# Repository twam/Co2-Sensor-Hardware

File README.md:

Co2-Sensor-Hardware
===

This repository is the hoftware part of the software project https://github.com/twam/Co2-Sensor-Software.

### Images

### JLCPCB

PCBs can be ordered almost fully-assembled from [JLCPCB](https://jlcpcb.com/DDE). Required files are
[Co2-Sensor_bom_jlc.csv](Gerber/Co2-Sensor_bom_jlc.csv), [Co2-Sensor_cpl_jlc.csv](Gerber/Co2-Sensor_cpl_jlc.csv) and
[Co2-Sensor.zip](Co2-Sensor.zip). Components missing are
* Co2 Sensor (J2)
* USB connector (J5) – can be also populated in the mean time, but is not included in production files, yet.

## License

[![CC BY-SA 4.0][cc-by-sa-shield]][cc-by-sa]

This work is licensed under a [Creative Commons Attribution-NonCommercial-ShareAlike 4.0 International License][cc-by-sa].

[![CC BY-SA 4.0][cc-by-sa-image]][cc-by-sa]

[cc-by-sa]: http://creativecommons.org/licenses/by-nc-sa/4.0/
[cc-by-sa-image]: https://licensebuttons.net/l/by-nc-sa/4.0/88x31.png
[cc-by-sa-shield]: https://img.shields.io/badge/License-CC%20BY--NC--SA%204.0-lightgrey.svg

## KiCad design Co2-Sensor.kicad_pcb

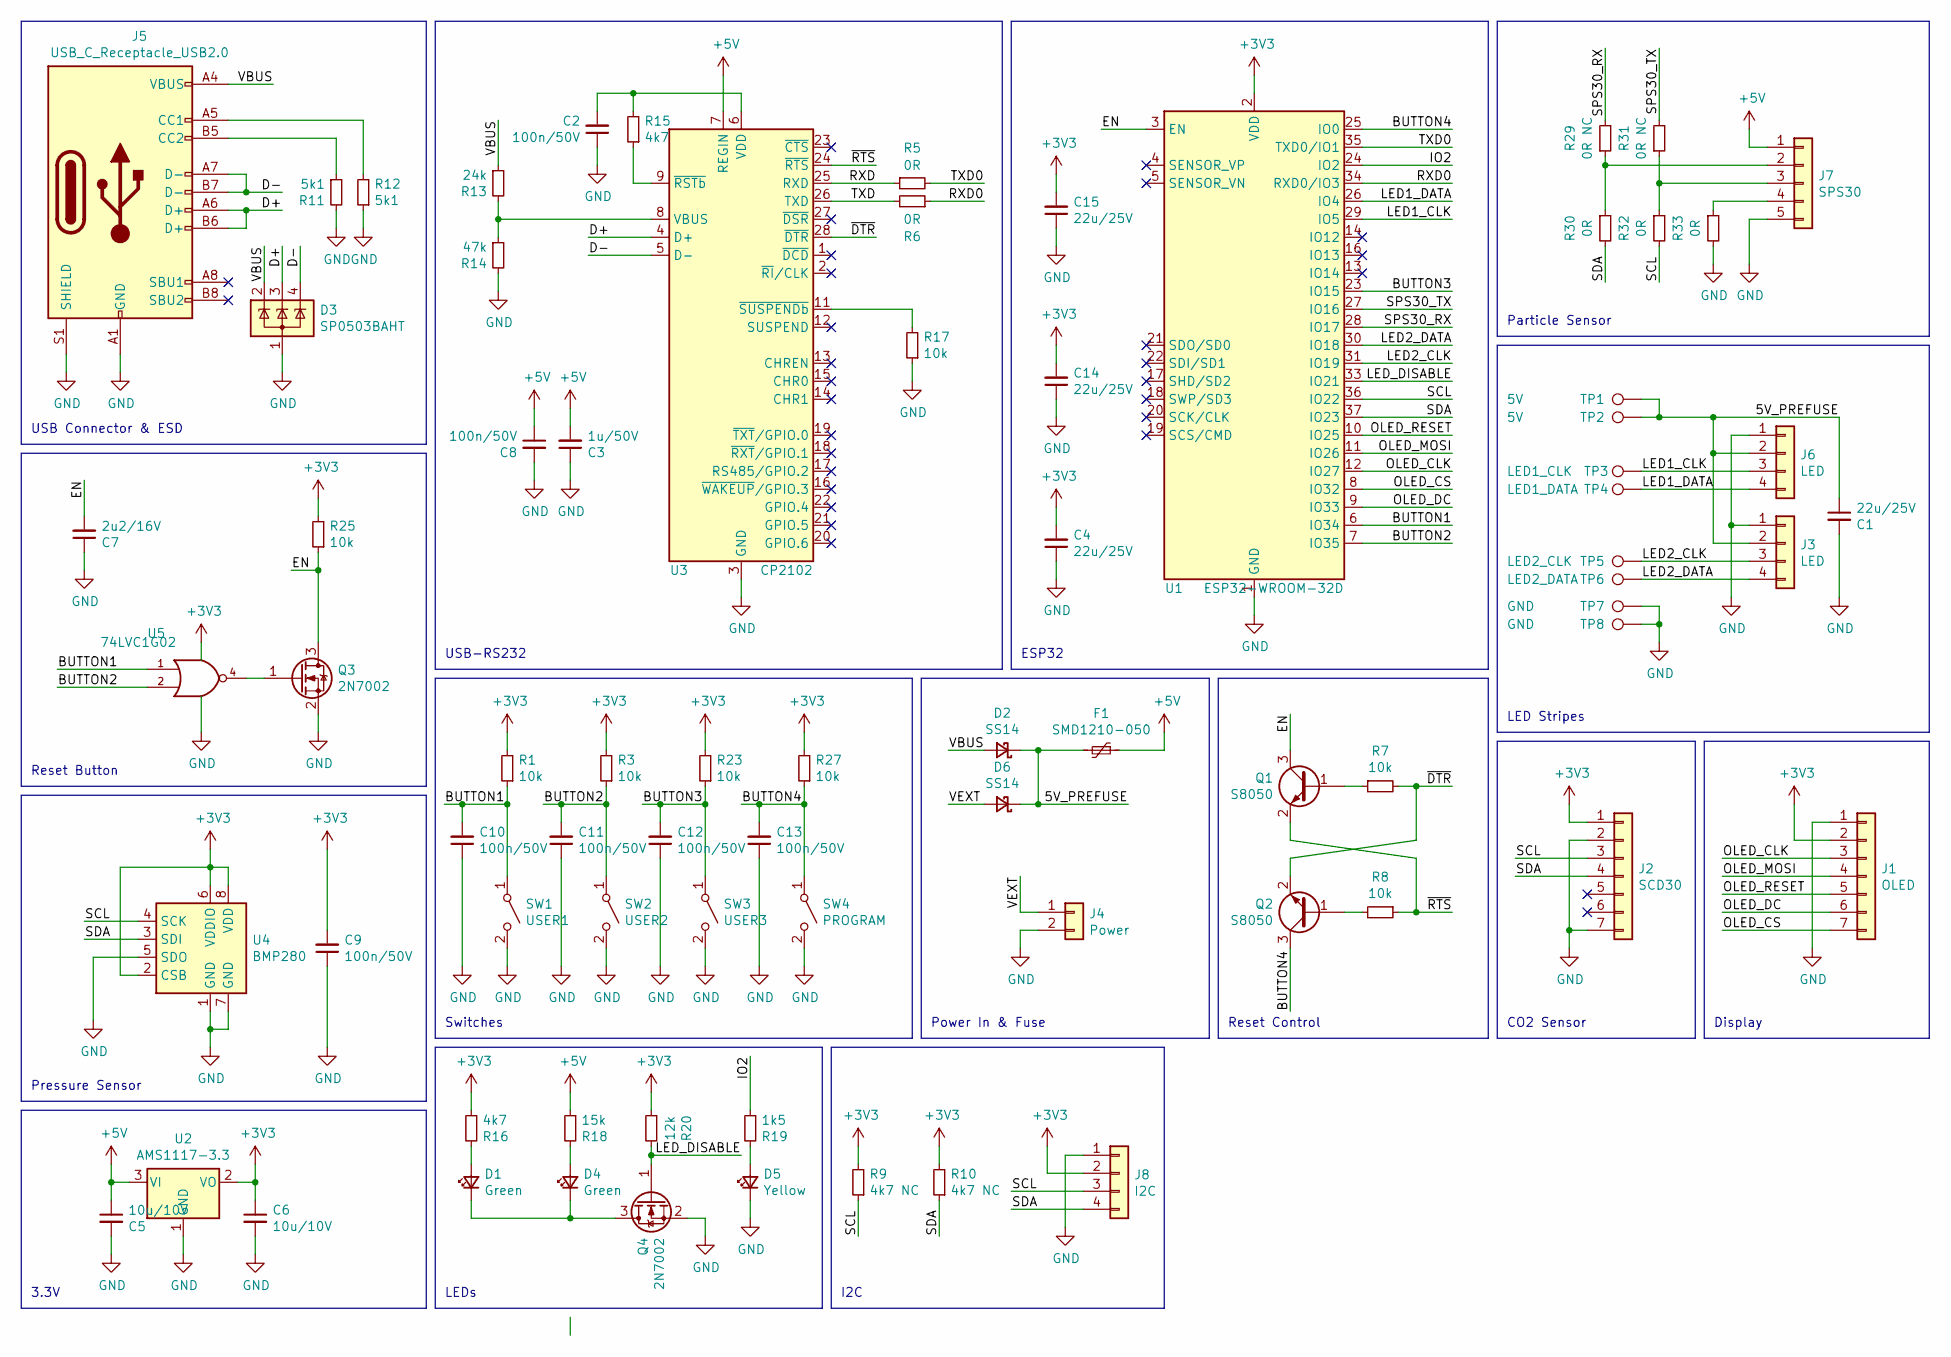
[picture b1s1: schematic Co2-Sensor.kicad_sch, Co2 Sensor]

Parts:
C1, C4, C14, C15: 22u/25V; C_0805_2012Metric; LCSC C45783
C2, C8, C9, C10, C11, C12, C13: 100n/50V; C_0603_1608Metric; LCSC C14663
C3: 1u/50V; C_0603_1608Metric; LCSC C15849
C5, C6: 10u/10V; C_0603_1608Metric; LCSC C19702
C7: 2u2/16V; C_0603_1608Metric; LCSC C23630
D1, D4: Green; LED_0603_1608Metric; LCSC C72043
D2, D6: SS14; D_SMA; LCSC C2480
D3: SP0503BAHT; SOT-143; LCSC C7074
D5: Yellow; LED_0603_1608Metric; LCSC C72038
F1: SMD1210-050; Fuse_1210_3225Metric; LCSC C70094
J1: OLED; TZT_154
J2: SCD30; Sensiron_SCD30
J3, J6: LED; PinHeader_1x04_P2.54mm_Horizontal
J4: Power; PinHeader_1x02_P2.54mm_Horizontal
J5: USB_C_Receptacle_USB2.0; USB_C_Receptacle_XKB_U262-16XN-4BVC11
J7: SPS30; PinHeader_1x05_P2.54mm_Horizontal
J8: I2C; PinHeader_1x04_P2.54mm_Horizontal
Q1, Q2: S8050; SOT-23; LCSC C2146
Q3, Q4: 2N7002; SOT-23; LCSC C8545
R1, R3, R7, R8, R17, R23, R25, R27: 10k; R_0603_1608Metric; LCSC C25804
R5, R6, R30, R32, R33: 0R; R_0603_1608Metric; LCSC C21189
R9, R10: 4k7 NC; R_0603_1608Metric
R11, R12: 5k1; R_0603_1608Metric; LCSC C23186
R13: 24k; R_0603_1608Metric; LCSC C23352
R14: 47k; R_0603_1608Metric; LCSC C25819
R15, R16: 4k7; R_0603_1608Metric; LCSC C23162
R18: 15k; R_0603_1608Metric; LCSC C22809
R19: 1k5; R_0603_1608Metric; LCSC C22843
R20: 12k; R_0603_1608Metric; LCSC C22790
R29, R31: 0R NC; R_0603_1608Metric
SW1: USER1; SW_SPST_XKB_TS-1187A-X-X-X; LCSC C318886
SW2: USER2; SW_SPST_XKB_TS-1187A-X-X-X; LCSC C318886
SW3: USER3; SW_SPST_XKB_TS-1187A-X-X-X; LCSC C318886
SW4: PROGRAM; SW_SPST_XKB_TS-1187A-X-X-X; LCSC C318886
TP1, TP2: 5V; TestPoint_Pad_2.5x2.5mm
TP3: LED1_CLK; TestPoint_Pad_2.5x2.5mm
TP4: LED1_DATA; TestPoint_Pad_2.5x2.5mm
TP5: LED2_CLK; TestPoint_Pad_2.5x2.5mm
TP6: LED2_DATA; TestPoint_Pad_2.5x2.5mm
TP7, TP8: GND; TestPoint_Pad_2.5x2.5mm
U1: ESP32-WROOM-32D; ESP32-WROOM-32
U2: AMS1117-3.3; SOT-223-3_TabPin2; LCSC C6186
U3: CP2102; QFN-28-1EP_5x5mm_P0.5mm_EP3.35x3.35mm; LCSC C6568
U4: BMP280; Bosch_LGA-8_2x2.5mm_P0.65mm_ClockwisePinNumbering; LCSC C83291
U5: 74LVC1G02; SOT-23-5; LCSC C16360

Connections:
+3V3: C4.2, C6.1, C9.2, C14.2, C15.2, J1.2, J2.1, J8.2, R1.2, R3.2, R9.2, R10.2, R16.1, R20.1, R23.2, R25.2, R27.2, U1.2 (VDD), U2.2 (VO), U4.2 (CSB), U4.6 (VDDIO), U4.8 (VDD), U5.5 (VCC)
+5V: C3.2, C5.1, C8.1, F1.1, J7.1, R18.1, U2.3 (VI), U3.7 (REGIN)
/5V_PREFUSE: C1.1, D2.1 (K), D6.1 (K), F1.2, J3.2, J6.2, TP1.1, TP2.1
/BUTTON1: C10.2, R1.1, SW1.1 (A), U1.6 (IO34), U5.1
/BUTTON2: C11.2, R3.1, SW2.1 (A), U1.7 (IO35), U5.2
/BUTTON3: C12.2, R23.1, SW3.1 (A), U1.23 (IO15)
/BUTTON4: C13.2, Q2.3 (C), R27.1, SW4.1 (A), U1.25 (IO0)
/D+: D3.3 (K), J5.A6 (D+), J5.B6 (D+), U3.4 (D+)
/D-: D3.4 (K), J5.A7 (D-), J5.B7 (D-), U3.5 (D-)
/EN: C7.2, Q1.3 (C), Q3.3 (D), R25.1, U1.3 (EN)
/IO2: R19.1, U1.24 (IO2)
/LED1_CLK: J6.3, TP3.1, U1.29 (IO5)
/LED1_DATA: J6.4, TP4.1, U1.26 (IO4)
/LED2_CLK: J3.3, TP5.1, U1.31 (IO19)
/LED2_DATA: J3.4, TP6.1, U1.30 (IO18)
/LED_DISABLE: Q4.1 (G), R20.2, U1.33 (IO21)
/OLED_CLK: J1.3, U1.12 (IO27)
/OLED_CS: J1.7, U1.8 (IO32)
/OLED_DC: J1.6, U1.9 (IO33)
/OLED_MOSI: J1.4, U1.11 (IO26)
/OLED_RESET: J1.5, U1.10 (IO25)
/RXD: R5.1, U3.25 (RXD)
/RXD0: R6.1, U1.34 (RXD0/IO3)
/SCL: J2.3, J8.3, R9.1, R32.2, U1.36 (IO22), U4.4 (SCK)
/SDA: J2.4, J8.4, R10.1, R30.2, U1.37 (IO23), U4.3 (SDI)
/SPS30_RX: R29.2, U1.28 (IO17)
/SPS30_TX: R31.2, U1.27 (IO16)
/TXD: R6.2, U3.26 (TXD)
/TXD0: R5.2, U1.35 (TXD0/IO1)
/VBUS: D2.2 (A), D3.2 (K), J5.A4 (VBUS), J5.A9 (VBUS), J5.B4 (VBUS), J5.B9 (VBUS), R13.1
/VEXT: D6.2 (A), J4.1
/~DTR: Q2.2 (E), R7.2, U3.28 (~DTR)
/~RTS: Q1.2 (E), R8.1, U3.24 (~RTS)
GND: C1.2, C2.1, C3.1, C4.1, C5.2, C6.2, C7.1, C8.2, C9.1, C10.1, C11.1, C12.1, C13.1, C14.1, C15.1, D3.1 (A), D5.1 (K), J1.1, J2.2, J2.7, J3.1, J4.2, J5.A1 (GND), J5.A12 (GND), J5.B1 (GND), J5.B12 (GND), J5.S1 (SHIELD), J6.1, J7.5, J8.1, Q3.2 (S), Q4.2 (S), R11.2, R12.1, R14.2, R17.1, R33.2, SW1.2 (B), SW2.2 (B), SW3.2 (B), SW4.2 (B), TP7.1, TP8.1, U1.1 (GND), U1.15 (GND), U1.38 (GND), U1.39 (GND), U2.1 (GND), U3.3 (GND), U3.29 (GND), U4.1 (GND), U4.5 (SDO), U4.7 (GND), U5.3 (GND)
unnamed: C2.2, R15.2, U3.6 (VDD)
unnamed: D1.1 (K), D4.1 (K), Q4.3 (D)
unnamed: D1.2 (A), R16.2
unnamed: D4.2 (A), R18.2
unnamed: D5.2 (A), R19.2
unnamed: J5.A5 (CC1), R12.2
unnamed: J5.B5 (CC2), R11.1
unnamed: J7.2, R29.1, R30.1
unnamed: J7.3, R31.1, R32.1
unnamed: J7.4, R33.1
unnamed: Q1.1 (B), R7.1
unnamed: Q2.1 (B), R8.2
unnamed: Q3.1 (G), U5.4
unnamed: R13.2, R14.1, U3.8 (VBUS)
unnamed: R15.1, U3.9 (~RSTb)
unnamed: R17.2, U3.11 (~SUSPENDb)

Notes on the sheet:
LED Stripes
I2C
Reset Control
CO2 Sensor
Switches
ESP32
Reset Button
Power In & Fuse
USB Connector & ESD
Particle Sensor
3.3V
USB-RS232
LEDs
Display
Pressure Sensor

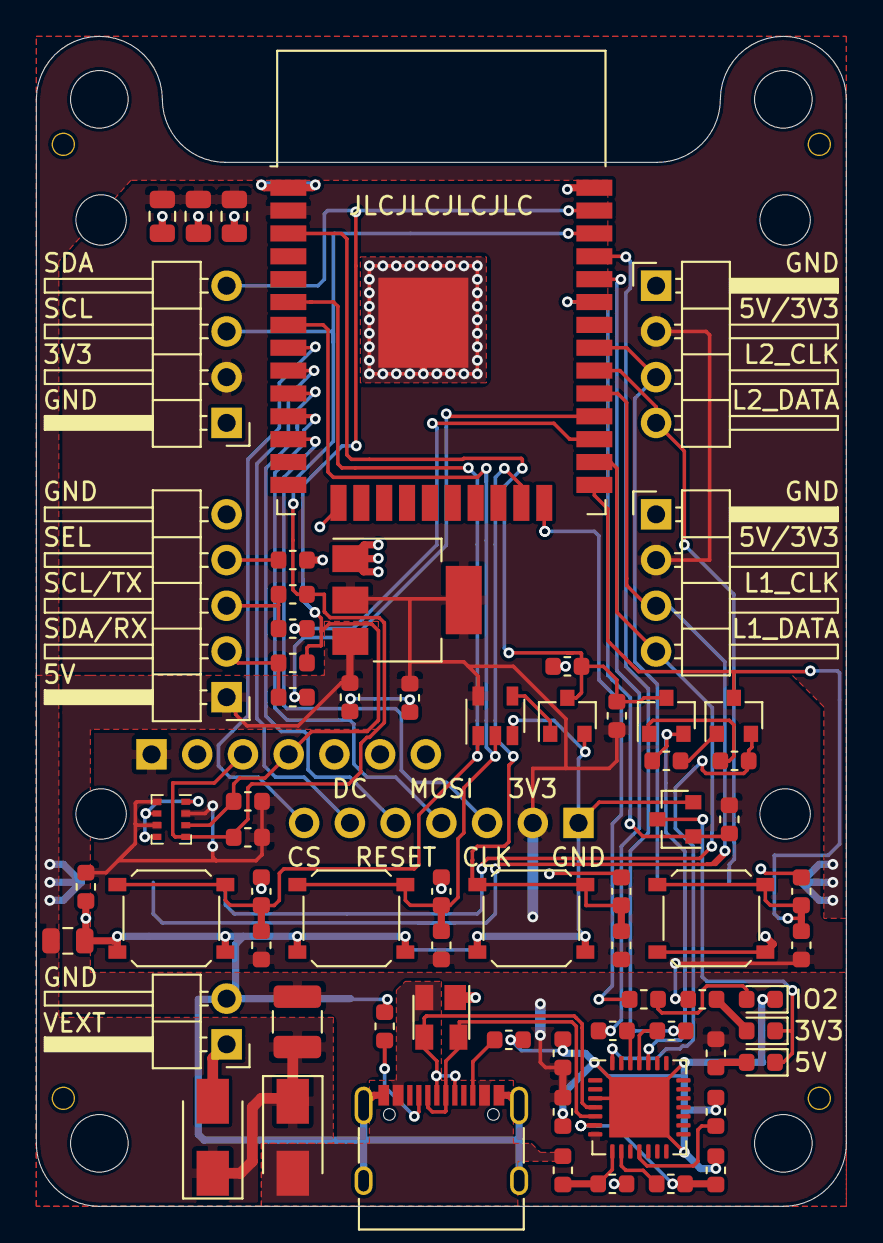
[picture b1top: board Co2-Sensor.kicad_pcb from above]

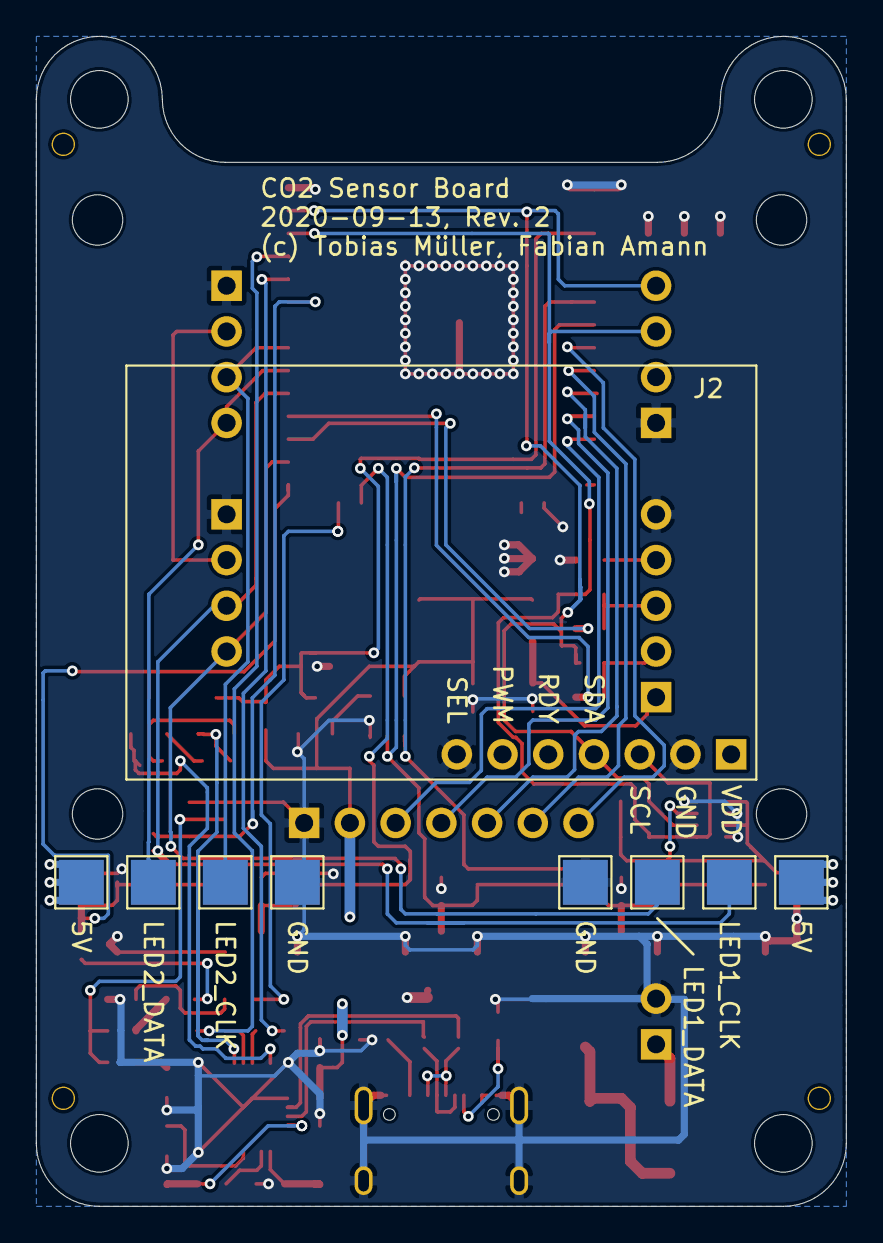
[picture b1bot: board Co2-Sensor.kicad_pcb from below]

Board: 2 copper layers, 45.0 x 65.0 mm, 77 parts (9 on the bottom side), 50 nets.

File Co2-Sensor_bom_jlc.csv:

"Comment","Designator","Footprint","LCSC Part #"
"100n/50V","C2,C8,C9,C10,C11,C12,C13","C_0603_1608Metric","C14663"
"1u/50V","C3","C_0603_1608Metric","C15849"
"22u/25V","C4,C1,C14,C15","C_0805_2012Metric","C45783"
"10u/10V","C5,C6","C_0603_1608Metric","C19702"
"2u2/16V","C7","C_0603_1608Metric","C23630"
"Green","D1,D4","LED_0603_1608Metric","C72043"
"SS14","D2,D6","D_SMA","C2480"
"SP0503BAHT","D3","SOT-143","C7074"
"Yellow","D5","LED_0603_1608Metric","C72038"
"SMD1210-050","F1","Fuse_1210_3225Metric","C70094"
"S8050","Q1,Q2","SOT-23","C2146"
"2N7002","Q3,Q4","SOT-23","C8545"
"0R","R5,R6,R33,R32,R30","R_0603_1608Metric","C21189"
"10k","R7,R8,R3,R1,R17,R23,R27,R25","R_0603_1608Metric","C25804"
"5k1","R12,R11","R_0603_1608Metric","C23186"
"24k","R13","R_0603_1608Metric","C23352"
"47k","R14","R_0603_1608Metric","C25819"
"4k7","R15,R16","R_0603_1608Metric","C23162"
"15k","R18","R_0603_1608Metric","C22809"
"1k5","R19","R_0603_1608Metric","C22843"
"12k","R20","R_0603_1608Metric","C22790"
"USER1","SW1","SW_SPST_XKB_TS-1187A-X-X-X","C318886"
"USER2","SW2","SW_SPST_XKB_TS-1187A-X-X-X","C318886"
"USER3","SW3","SW_SPST_XKB_TS-1187A-X-X-X","C318886"
"PROGRAM","SW4","SW_SPST_XKB_TS-1187A-X-X-X","C318886"
"AMS1117-3.3","U2","SOT-223-3_TabPin2","C6186"
"CP2102","U3","QFN-28-1EP_5x5mm_P0.5mm_EP3.35x3.35mm","C6568"
"74LVC1G02","U5","SOT-23-5","C16360"

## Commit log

2020-10-02 Add changes for Rev. 2
2020-10-03 Minor improvements
2020-10-04 Add more capacitance to ESP
2020-11-05 Revision 2
2020-11-05 Add schematic as PDF
2020-11-05 Add Readme
2020-11-11 Add case
2020-11-13 Add images
2021-12-06 Add more case variants
2022-01-07 Move JLCPCB files to Gerber
2022-01-07 Improve README
2022-01-07 Update to KiCad 6
